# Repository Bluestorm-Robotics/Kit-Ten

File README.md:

# The best readme to ever exist
This is the start of the coolest github repository

Bluestorm Robotics Robocup Jr line-rescue 2024.
Programmed by bellatheITgirl

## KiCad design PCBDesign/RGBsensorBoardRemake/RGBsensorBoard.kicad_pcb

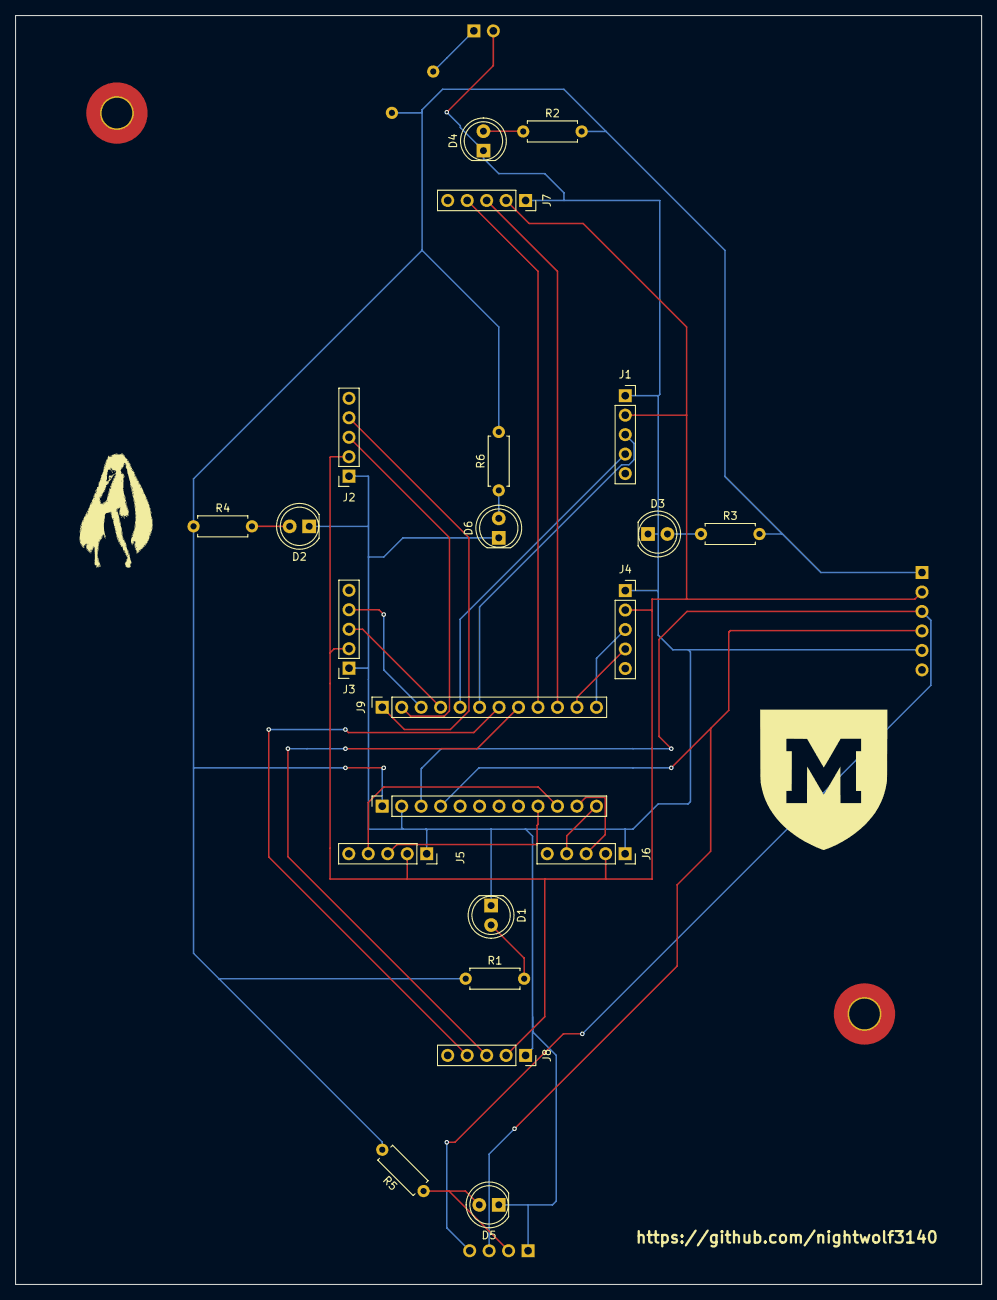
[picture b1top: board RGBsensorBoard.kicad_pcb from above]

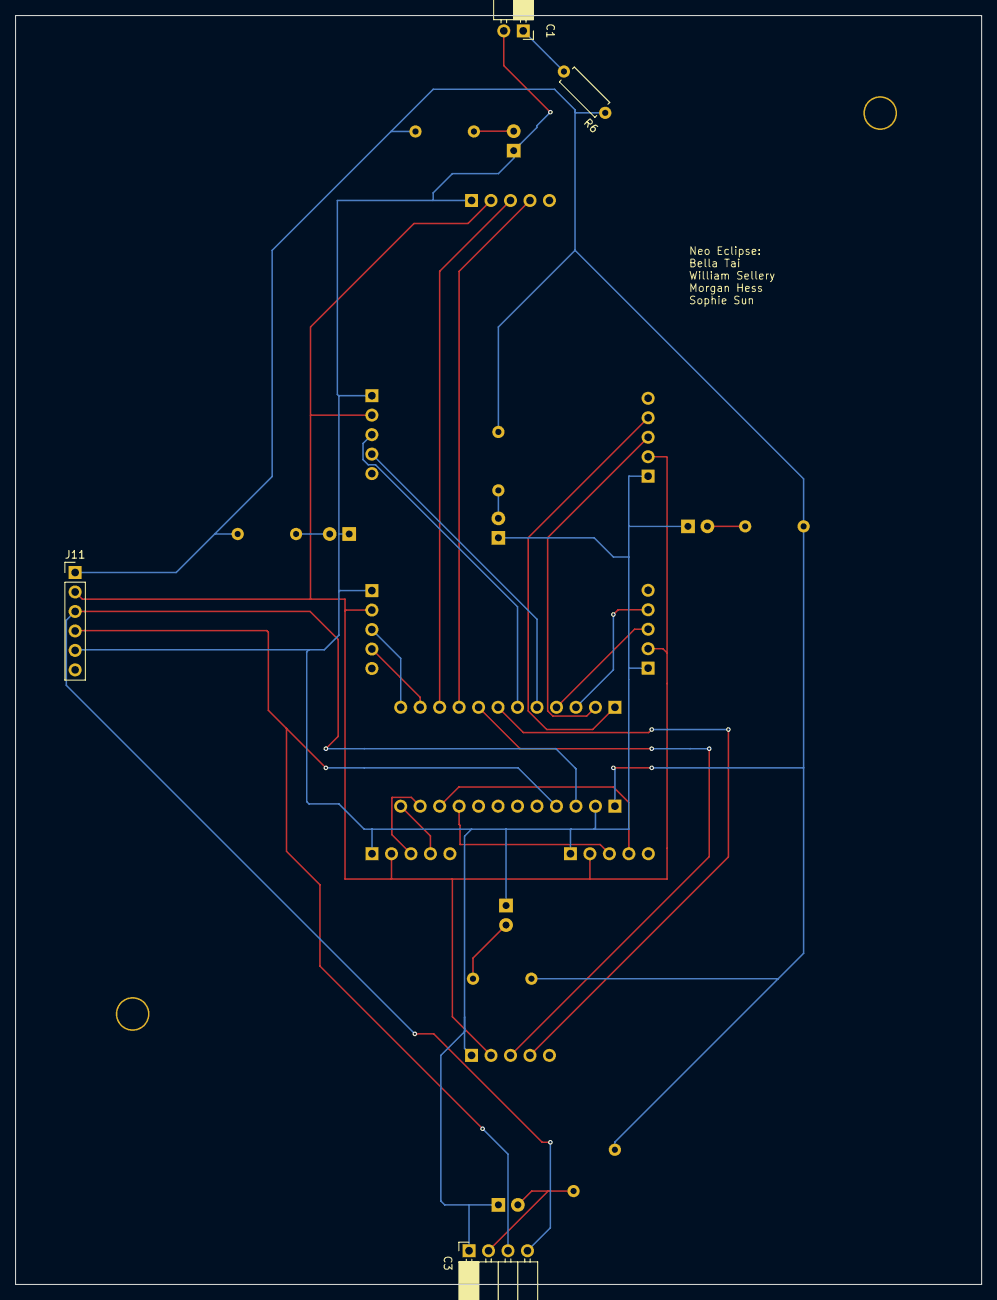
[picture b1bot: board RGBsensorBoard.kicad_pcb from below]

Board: 2 copper layers, 126.0 x 165.5 mm, 28 parts (4 on the bottom side), 21 nets.

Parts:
C1: Conn_01x05_Socket; PinSocket_1x02_P2.54mm_Horizontal
C3: Conn_01x05_Socket; PinSocket_1x04_P2.54mm_Horizontal
D1, D2, D3, D4, D5, D6: LED; LED_D5.0mm
J1, J2, J3, J4, J5, J6, J7, J8: Conn_01x05_Socket; PinSocket_1x05_P2.54mm_Vertical
J9, J10: Multiplexer Conn_01x12_Socket; PinSocket_1x12_P2.54mm_Vertical
J11: Conn_01x05_Pin; PinHeader_1x06_P2.54mm_Vertical
R1, R2, R3, R4, R5, R6, R6#2: R_Variable_US; R_Axial_DIN0207_L6.3mm_D2.5mm_P7.62mm_Horizontal
hole, hole2: MountingHole_4mm_Pad_TopOnly

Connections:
3.3: J1.2, J2.2, J3.2, J4.2, J5.2, J6.2, J7.2, J8.2, J11.2
/GND: C1.2, C3.1, D1.1 (K), D2.1 (K), D3.1 (K), D4.1 (K), D5.1 (K), D6.1 (K), J1.1, J2.1, J3.1, J4.1, J5.1, J6.1, J7.1, J8.1, J10.2, J11.5
/SC0: J5.4, J10.10
/SC2: J4.4, J9.11
/SC3: J7.4, J9.9
/SC4: J8.4, J9.7
/SC5: J1.4, J9.5
/SC6: J3.4, J9.3
/SC7: J2.4, J9.1
/SCL: C3.3, J10.4, J11.4
/SD0: J5.3, J10.9
/SD1: J6.3, J10.11
/SD2: J4.3, J9.12
/SD3: J7.3, J9.10
/SD4: J8.3, J9.8
/SD5: J1.3, J9.6
/SD6: J3.3, J9.4
/SD7: J2.3, J9.2
/SDA: C3.4, J10.3, J11.3
/VIN 5V: C1.1, C3.2, D1.2 (A), D2.2 (A), D3.2 (A), D4.2 (A), D5.2 (A), D6.2 (A), J10.1, J11.1, J11.6, R1.1, R1.2, R2.1, R2.2, R3.1, R3.2, R4.1, R4.2, R5.1, R5.2, R6.1, R6.2, R6#2.1, R6#2.2
SC1: J6.4, J10.12

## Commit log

2024-03-19 Arduino test files added
    I hope this works :)
2024-03-19 added readme
2024-03-19 added liscence
2024-03-20 servo shield please
2024-03-20 motors working
2024-03-22 Create unstable_tester
2024-03-22 put unstable in ino
2024-03-23 ultrasonic sensor
    also moved files out of testing folder
2024-03-26 Added DCMotor
2024-03-26 past edits
    i forget whats happening here actually
2024-03-26 added light sensor example
2024-03-27 light and speed
2024-03-27 incorporating ultrasonic
2024-03-27 run with ultrasonic
2024-04-02 control driving
2024-04-06 on/off buttons
2024-04-09 Add files via upload
    want a second look over on this
2024-04-12 color sensors file
2024-04-13 multiplexer
2024-04-13 3 working sensors
    ports 0 1 2
2024-04-18 nicla testing
    gyro + accelerometer + proximity
2024-04-25 motor shield code
2024-04-26 run 3 shields 6 motors
2024-04-26 8 color sensors
2024-04-26 navcode
    making nav code
2024-04-26 arrays
    i love iterating through things
2024-04-28 motor driving
2024-04-29 driving
    sixsteppers has forwards test, navigate has beginning of navigation code (help)
2024-04-30 logic tree and double motors
2024-05-02 fwddriving
2024-05-02 new batteries
2024-05-02 changed max speed to variable
2024-05-02 code comments to comedic effect
2024-05-03 may 3
2024-05-04 calibration pt 1
2024-05-07 new shields
2024-05-07 four motors
2024-05-08 new nav
2024-05-09 update
    alternating steps
2024-05-09 running
2024-05-10 fixed compiler error and reviewed code :D
2024-05-10 added PCB design files in new folder
2024-05-10 line tracking
2024-05-12 new code for new prototype
    four dc motors with two drivers
2024-05-12 200 makes the ramp work
    YIPPEE
2024-05-13 driving
2024-05-15 truth table & calibration
2024-05-15 calibrate good times cmon
    lets calibrate ~(^-^)~
2024-05-16 testing
2024-05-16 what are you doing
    simple line follower
2024-05-16 wahhhh
2024-05-16 timer test code
2024-05-17 fixed leftbkw adn leftfwd pointing back to eachother forever
2024-05-17 fixed uncommented code
2024-05-17 sorta ish almost working but no calibrate :(
2024-05-17 pid incorporation
2024-05-17 extremely basic linetracking sorta
2024-05-17 testing sensor
2024-05-17 so uh encoder no read direction uh oh
2024-05-18 last night
2024-05-18 yay it work now but not really
2024-05-18 new stuff to calibrate mids
2024-05-18 turns
2024-05-18 calibration stuffs
2024-05-18 while multiplexer update
2024-05-18 remove +50
2024-05-18 fixed merge issue
2024-05-18 front sensor check
2024-05-18 front is calibrated
2024-05-18 added little step
2024-05-18 error: Your local changes to the followin files would be overwritten by merge: fourdc/fourdc.ino
2024-05-18 changes today
2024-05-19 what are you doing
2024-05-19 no more speed changes
2024-05-19 go away big turn
2024-05-19 slightly better ?!
2025-10-02 Added Tech papaer
    forgot to add this, then im archiving it permenatly
